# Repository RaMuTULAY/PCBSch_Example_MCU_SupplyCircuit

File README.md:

# PCBSch_Example_MCU_SupplyCircuit
Part of a PCB, supply circuit 24V to 5V smps buck converter MAX20076DATCA

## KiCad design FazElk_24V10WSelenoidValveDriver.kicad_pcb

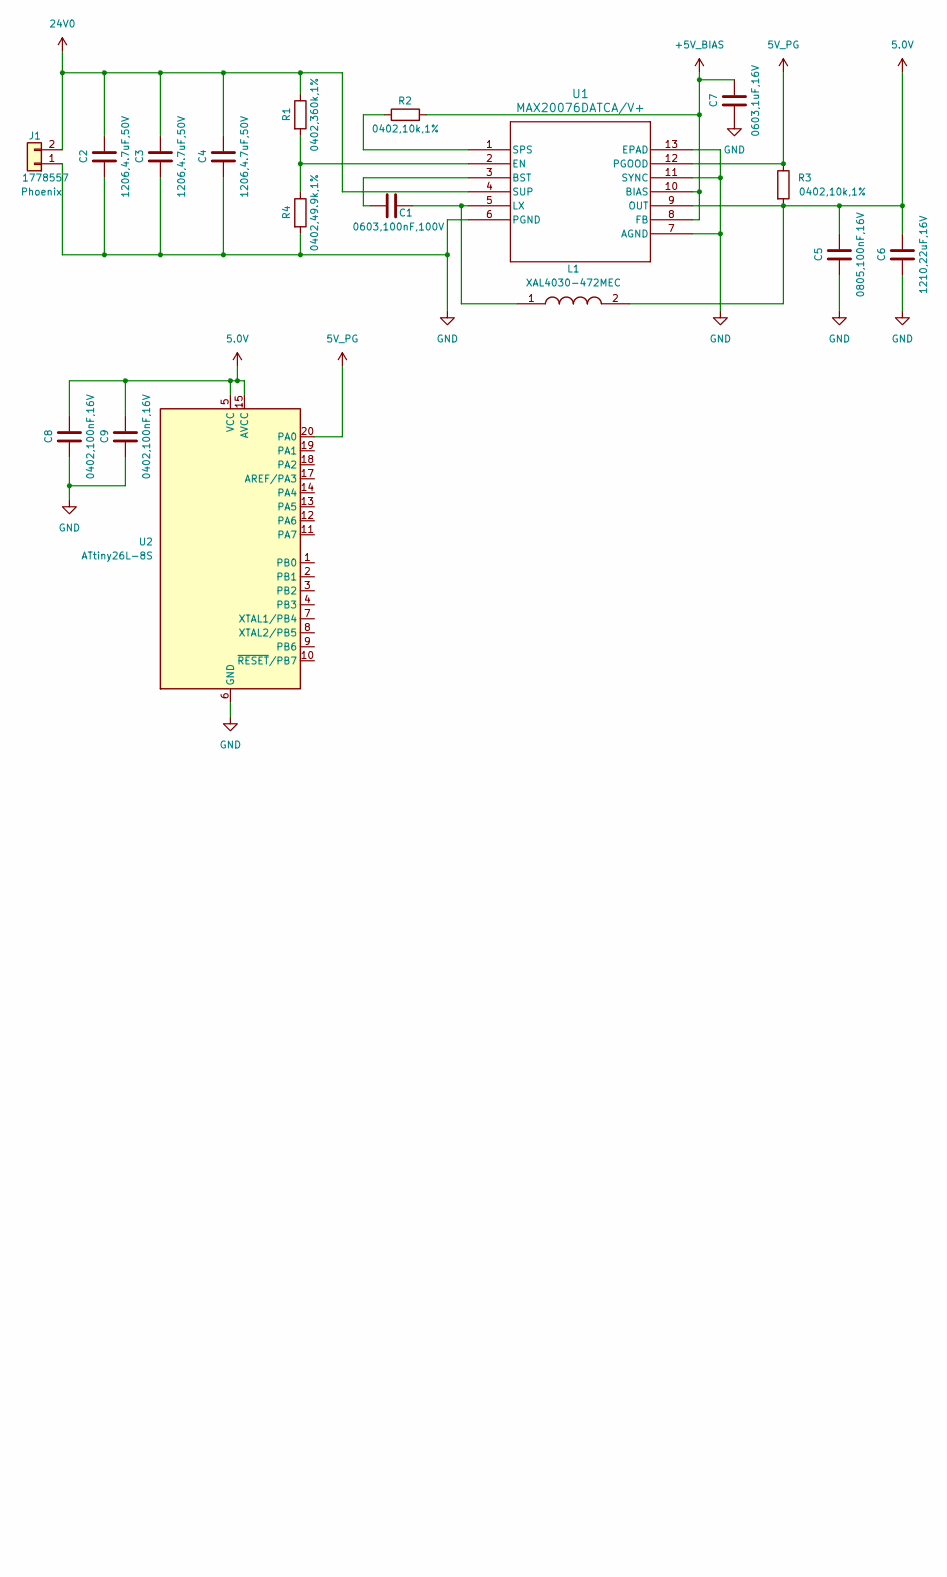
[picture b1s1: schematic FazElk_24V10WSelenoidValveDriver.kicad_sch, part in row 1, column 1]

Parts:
C1, C7: C; C_0603_1608Metric
C2, C3, C4: C; C_1206_3216Metric
C5: 100nF; C_0805_2012Metric
C6: 22uF; C_1210_3225Metric
C8, C9: C; C_0402_1005Metric
J1: 1778557; PhoenixContact_MSTBVA_2,5_2-G_1x02_P5.00mm_Vertical
L1: XAL4030-472MEC; XAL4030472MEC; Mouser Part Number 994-XAL4030-472MEC
R1, R2, R3, R4: R; R_0402_1005Metric
U1: MAX20076DATCA/V+; 21-0664E_MXM
U2: ATtiny26L-8S; SOIC-20W_7.5x12.8mm_P1.27mm

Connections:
5.0V: C5.1, C6.1, C8.1, C9.1, L1.2, R3.2, U1.9 (OUT), U2.5 (VCC), U2.15 (AVCC)
5V_PG: R3.1, U1.12 (PGOOD), U2.20 (PA0)
24V0: C2.1, C3.1, C4.1, J1.2, R1.1, U1.4 (SUP)
+5V_BIAS: C7.1, R2.2, U1.8 (FB), U1.10 (BIAS)
GND: C2.2, C3.2, C4.2, C5.2, C6.2, C7.2, C8.2, C9.2, J1.1, R4.2, U1.6 (PGND), U1.7 (AGND), U1.11 (SYNC), U1.13 (EPAD), U2.6 (GND), U2.16 (GND)
unnamed: C1.2, U1.3 (BST)
unnamed: R1.2, R4.1, U1.2 (EN)
unnamed: C1.1, L1.1, U1.5 (LX)
unnamed: R2.1, U1.1 (SPS)

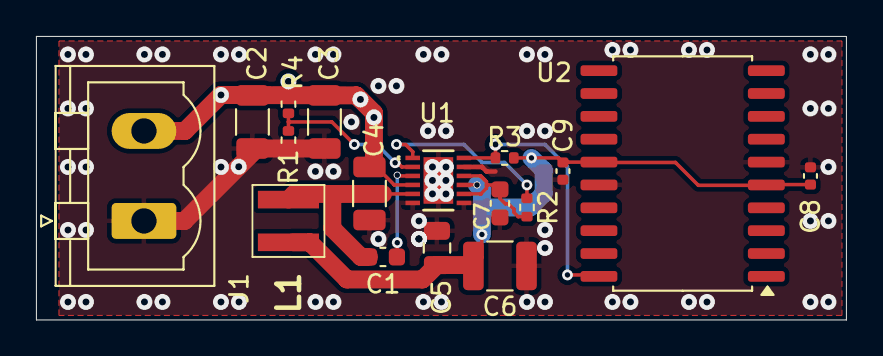
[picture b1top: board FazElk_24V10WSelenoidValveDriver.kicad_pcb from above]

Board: 4 copper layers, 45.0 x 15.8 mm, 17 parts (0 on the bottom side), 9 nets.
